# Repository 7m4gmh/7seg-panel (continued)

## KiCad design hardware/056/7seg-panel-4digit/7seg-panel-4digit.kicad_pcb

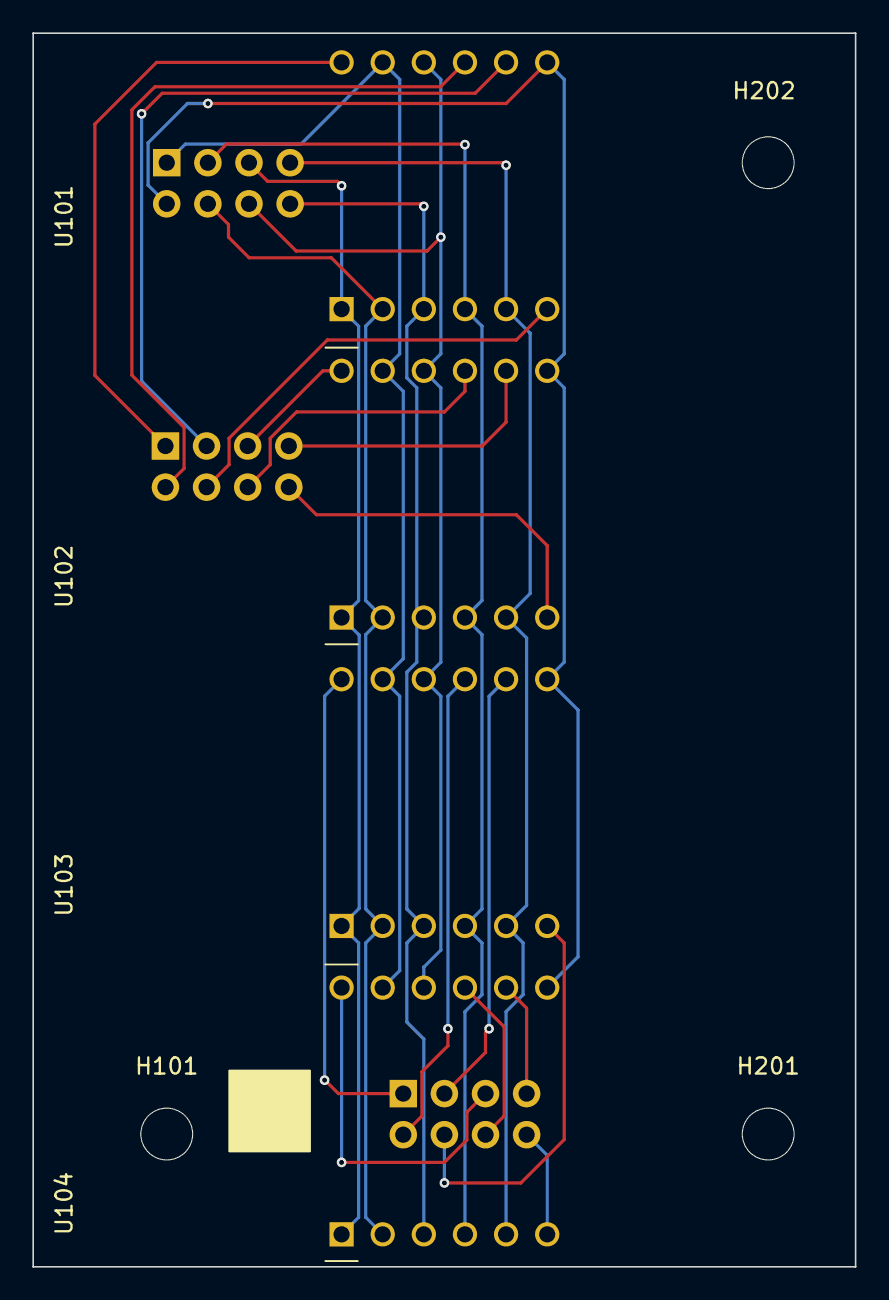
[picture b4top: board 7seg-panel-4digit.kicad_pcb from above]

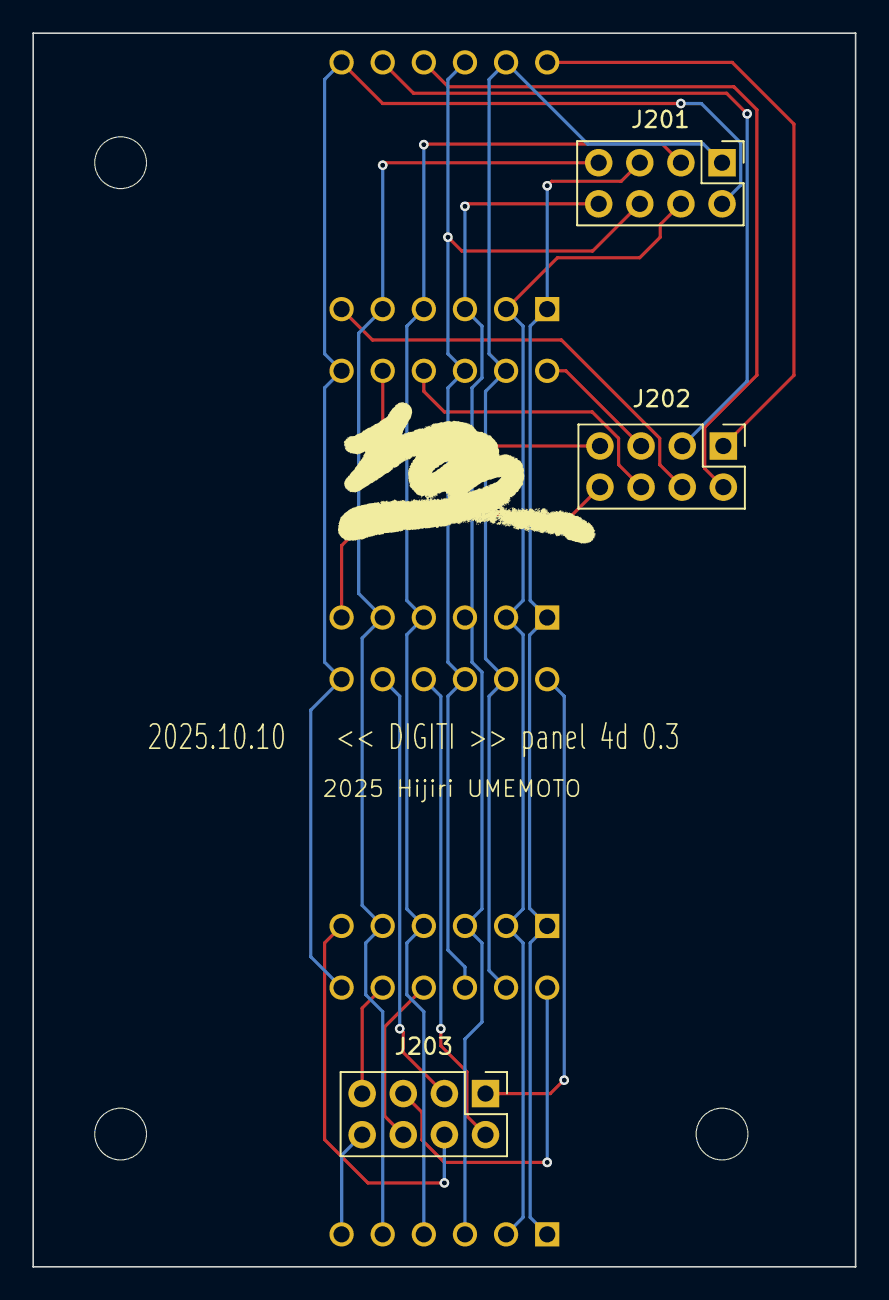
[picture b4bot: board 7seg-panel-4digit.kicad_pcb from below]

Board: 2 copper layers, 50.8 x 76.2 mm, 10 parts (3 on the bottom side), 24 nets.

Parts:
H101, H201, H202: MountingHole; MountingHole_3.2mm_M3
J201, J202, J203: Conn_02x04_Odd_Even; PinHeader_2x04_P2.54mm_Vertical
U101, U102, U103, U104: CA56-12EWA

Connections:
COM0: J201.1, U101.11 (a), U102.11 (a), U103.11 (a), U104.11 (a)
COM1: J201.2, U101.7 (b), U102.7 (b), U103.7 (b), U104.7 (b)
COM2: J201.3, U101.4 (c), U102.4 (c), U103.4 (c), U104.4 (c)
COM3: J201.4, U101.2 (d), U102.2 (d), U103.2 (d), U104.2 (d)
COM4: J201.5, U101.1 (e), U102.1 (e), U103.1 (e), U104.1 (e)
COM5: J201.6, U101.10 (f), U102.10 (f), U103.10 (f), U104.10 (f)
COM6: J201.7, U101.5 (g), U102.5 (g), U103.5 (g), U104.5 (g)
COM7: J201.8, U101.3 (DPX), U102.3 (DPX), U103.3 (DPX), U104.3 (DPX)
ROW0: J202.1, U101.12 (CA1)
ROW1: J202.2, U101.9 (CA2)
ROW2: J202.3, U101.8 (CA3)
ROW3: J202.4, U101.6 (CA4)
ROW4: J202.5, U102.12 (CA1)
ROW5: J202.6, U102.9 (CA2)
ROW6: J202.7, U102.8 (CA3)
ROW7: J202.8, U102.6 (CA4)
ROW8: J203.1, U103.12 (CA1)
ROW9: J203.2, U103.9 (CA2)
ROW10: J203.3, U103.8 (CA3)
ROW11: J203.4, U103.6 (CA4)
ROW12: J203.5, U104.12 (CA1)
ROW13: J203.6, U104.9 (CA2)
ROW14: J203.7, U104.8 (CA3)
ROW15: J203.8, U104.6 (CA4)

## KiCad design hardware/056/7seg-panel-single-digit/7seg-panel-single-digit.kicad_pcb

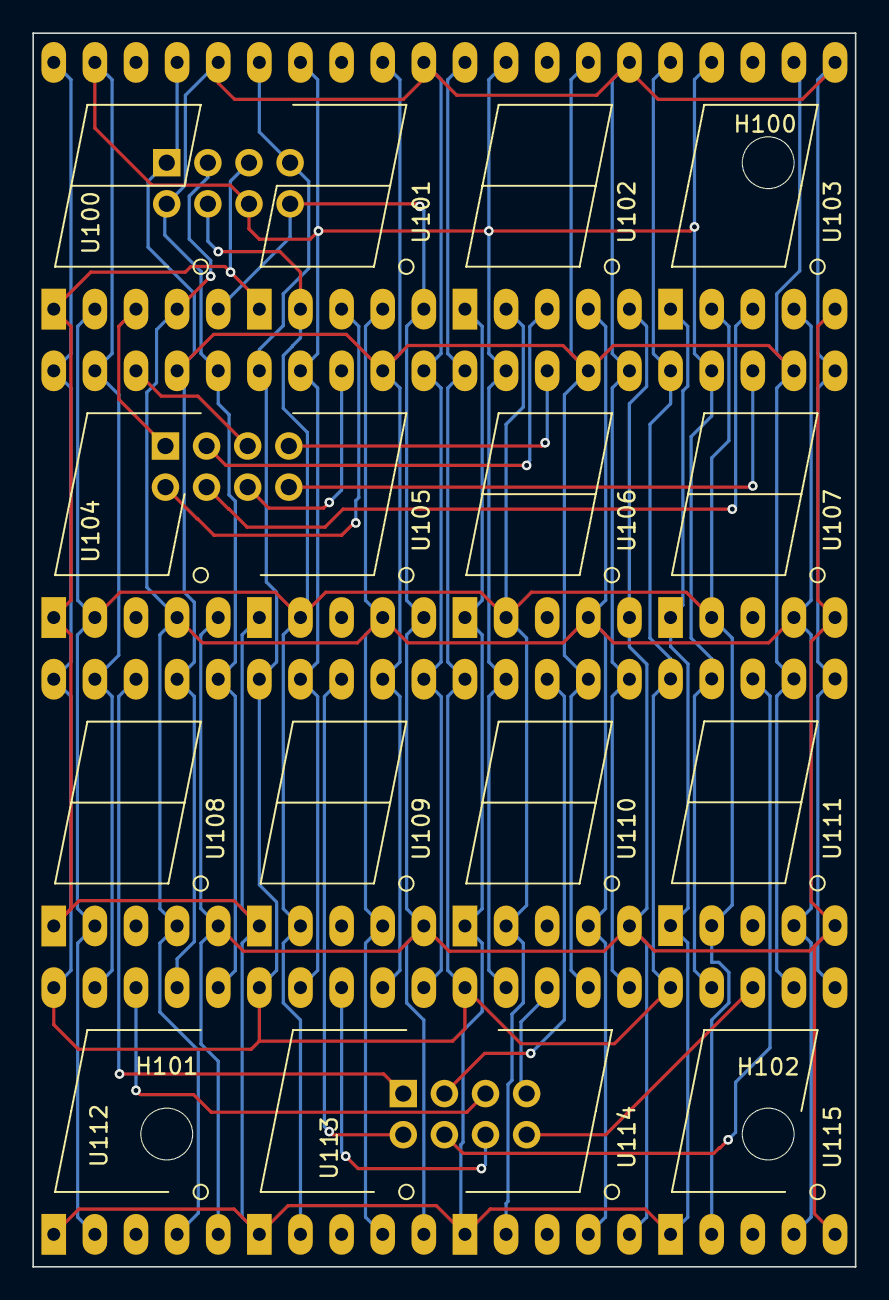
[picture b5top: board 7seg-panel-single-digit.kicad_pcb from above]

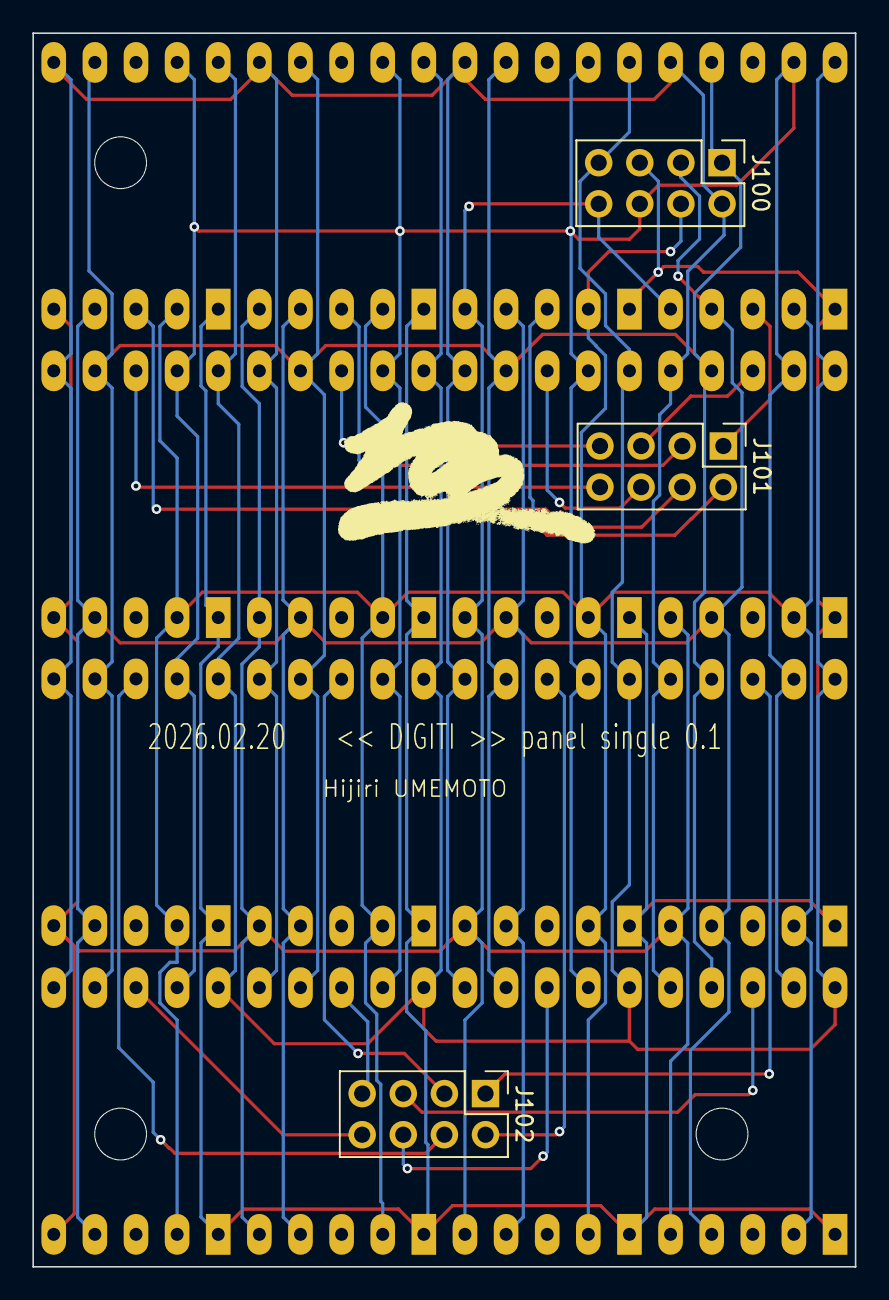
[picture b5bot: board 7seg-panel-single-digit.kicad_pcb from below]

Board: 2 copper layers, 50.8 x 76.2 mm, 22 parts (3 on the bottom side), 24 nets.

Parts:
H100, H101, H102: MountingHole; MountingHole_3.2mm_M3
J100, J101, J102: Conn_02x04_Odd_Even; PinHeader_2x04_P2.54mm_Vertical
U100, U101, U102, U103, U104, U105, U106, U107, U108, U109, U110, U111, U112, U113, U114, U115: OSL10564-IRA; 7SegmentLED_OSL10564

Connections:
COM0: J100.1, U100.7 (A), U101.7 (A), U102.7 (A), U103.7 (A), U104.7 (A), U105.7 (A), U106.7 (A), U107.7 (A), U108.7 (A), U109.7 (A), U110.7 (A), U111.7 (A), U112.7 (A), U113.7 (A), U114.7 (A), U115.7 (A)
COM1: J100.2, U100.6 (B), U101.6 (B), U102.6 (B), U103.6 (B), U104.6 (B), U105.6 (B), U106.6 (B), U107.6 (B), U108.6 (B), U109.6 (B), U110.6 (B), U111.6 (B), U112.6 (B), U113.6 (B), U114.6 (B), U115.6 (B)
COM2: J100.3, U100.4 (C), U101.4 (C), U102.4 (C), U103.4 (C), U104.4 (C), U105.4 (C), U106.4 (C), U107.4 (C), U108.4 (C), U109.4 (C), U110.4 (C), U111.4 (C), U112.4 (C), U113.4 (C), U114.4 (C), U115.4 (C)
COM3: J100.4, U100.2 (D), U101.2 (D), U102.2 (D), U103.2 (D), U104.2 (D), U105.2 (D), U106.2 (D), U107.2 (D), U108.2 (D), U109.2 (D), U110.2 (D), U111.2 (D), U112.2 (D), U113.2 (D), U114.2 (D), U115.2 (D)
COM4: J100.5, U100.1 (E), U101.1 (E), U102.1 (E), U103.1 (E), U104.1 (E), U105.1 (E), U106.1 (E), U107.1 (E), U108.1 (E), U109.1 (E), U110.1 (E), U111.1 (E), U112.1 (E), U113.1 (E), U114.1 (E), U115.1 (E)
COM5: J100.6, U100.9 (F), U101.9 (F), U102.9 (F), U103.9 (F), U104.9 (F), U105.9 (F), U106.9 (F), U107.9 (F), U108.9 (F), U109.9 (F), U110.9 (F), U111.9 (F), U112.9 (F), U113.9 (F), U114.9 (F), U115.9 (F)
COM6: J100.7, U100.10 (G), U101.10 (G), U102.10 (G), U103.10 (G), U104.10 (G), U105.10 (G), U106.10 (G), U107.10 (G), U108.10 (G), U109.10 (G), U110.10 (G), U111.10 (G), U112.10 (G), U113.10 (G), U114.10 (G), U115.10 (G)
COM7: J100.8, U100.5 (DP), U101.5 (DP), U102.5 (DP), U103.5 (DP), U104.5 (DP), U105.5 (DP), U106.5 (DP), U107.5 (DP), U108.5 (DP), U109.5 (DP), U110.5 (DP), U111.5 (DP), U112.5 (DP), U113.5 (DP), U114.5 (DP), U115.5 (DP)
ROW0: J101.1, U100.3 (CA)
ROW1: J101.2, U101.3 (CA)
ROW2: J101.3, U102.3 (CA)
ROW3: J101.4, U103.3 (CA)
ROW4: J101.5, U104.8 (CA)
ROW5: J101.6, U105.8 (CA)
ROW6: J101.7, U106.8 (CA)
ROW7: J101.8, U107.8 (CA)
ROW8: J102.1, U108.8 (CA)
ROW9: J102.2, U109.8 (CA)
ROW10: J102.3, U110.8 (CA)
ROW11: J102.4, U111.8 (CA)
ROW12: J102.5, U112.8 (CA)
ROW13: J102.6, U113.8 (CA)
ROW14: J102.7, U114.8 (CA)
ROW15: J102.8, U115.8 (CA)

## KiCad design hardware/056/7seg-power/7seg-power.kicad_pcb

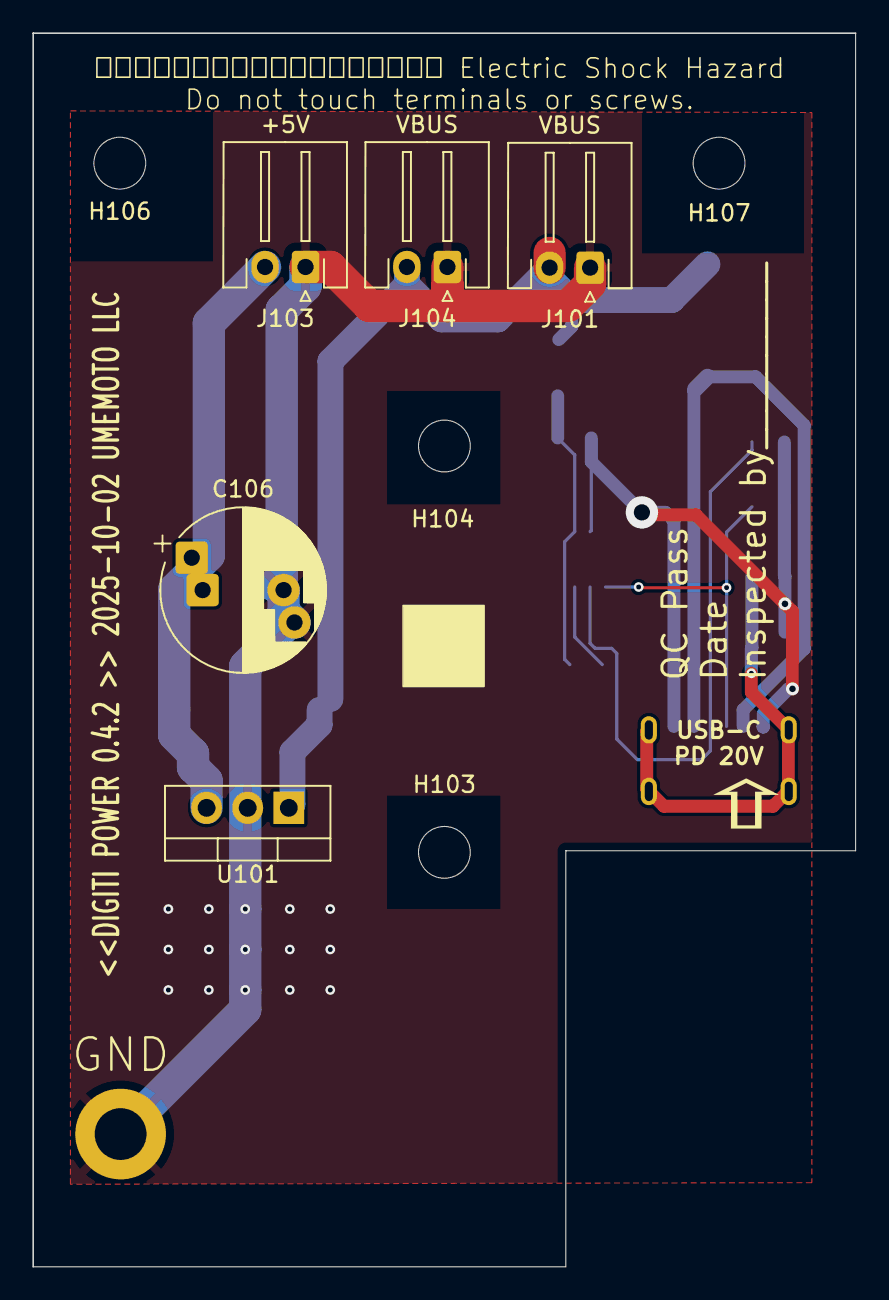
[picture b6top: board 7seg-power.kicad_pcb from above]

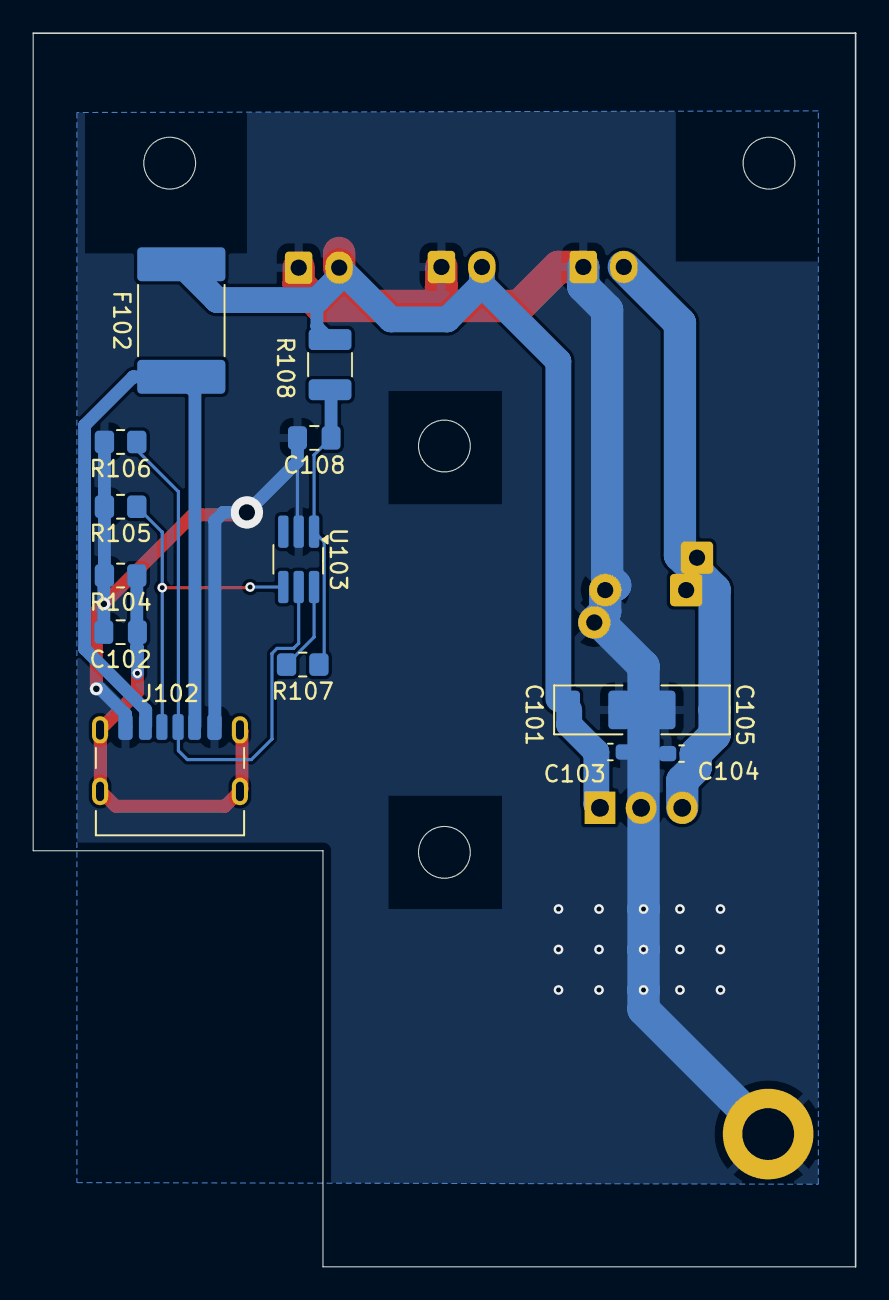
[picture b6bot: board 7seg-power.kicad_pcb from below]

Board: 2 copper layers, 50.8 x 76.2 mm, 24 parts (14 on the bottom side), 9 nets.

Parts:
C101, C105: 22uF; CP_EIA-3528-21_Kemet-B
C102: 4700pF (472); C_0805_2012Metric_Pad1.18x1.45mm_HandSolder
C103: 22uF 25V; C_0603_1608Metric_Pad1.08x0.95mm_HandSolder
C104: 22uF 6V; C_0603_1608Metric_Pad1.08x0.95mm_HandSolder
C106: 220uF; CP_Radial_D10.0mm_P5.00mm_P7.50mm
C108: 1uF; C_0805_2012Metric_Pad1.18x1.45mm_HandSolder
F102: Polyfuse 4A; Fuse_2920_7451Metric_Pad2.10x5.45mm_HandSolder
H102: GND; MountingHole_3.2mm_M3_DIN965_Pad
H103, H104, H106, H107: MountingHole; MountingHole_3.2mm_M3
J101, J104: VBUS; Generic_XH_S2B-XH-A-1_1x02_P2.50mm_Horizontal
J102: USB_C_Receptacle_PowerOnly_6P; USB_C_Receptacle_HRO_TYPE-C-31-M-17
J103: +5V; Generic_XH_S2B-XH-A-1_1x02_P2.50mm_Horizontal
R104: 1MR; R_0805_2012Metric_Pad1.20x1.40mm_HandSolder
R105, R106: 5k1R; R_0805_2012Metric_Pad1.20x1.40mm_HandSolder
R107: 200kR; R_0805_2012Metric_Pad1.20x1.40mm_HandSolder
R108: 1kR; R_1210_3225Metric_Pad1.30x2.65mm_HandSolder
U101: K7805M-2000; TO-220-3_Vertical
U103: CH221K; TSOT-23-6_HandSoldering

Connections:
+5V: C104.1, C105.1, C106.1, J103.2, U101.3 (VO)
GND: C101.2, C102.2, C103.2, C104.2, C105.2, C106.2, C108.2, H102.1 (MP), J101.1, J102.A12 (GND), J102.B12 (GND), J103.1, J104.1, R104.2, R105.2, R106.2, U101.2 (GND), U103.2 (GND)
unnamed: F102.1, J102.A9 (VBUS), J102.B9 (VBUS)
unnamed: J102.A5 (CC1), R105.1, U103.4 (CC1)
unnamed: J102.B5 (CC2), R106.1, U103.5 (CC2)
unnamed: C102.1, J102.S1 (SHIELD), R104.1
unnamed: R107.2, U103.6 (CFG)
unnamed: C108.1, R107.1, R108.1, U103.1 (VDD)
VBUS: C101.1, C103.1, F102.2, J101.2, J104.2, R108.2, U101.1 (VI)

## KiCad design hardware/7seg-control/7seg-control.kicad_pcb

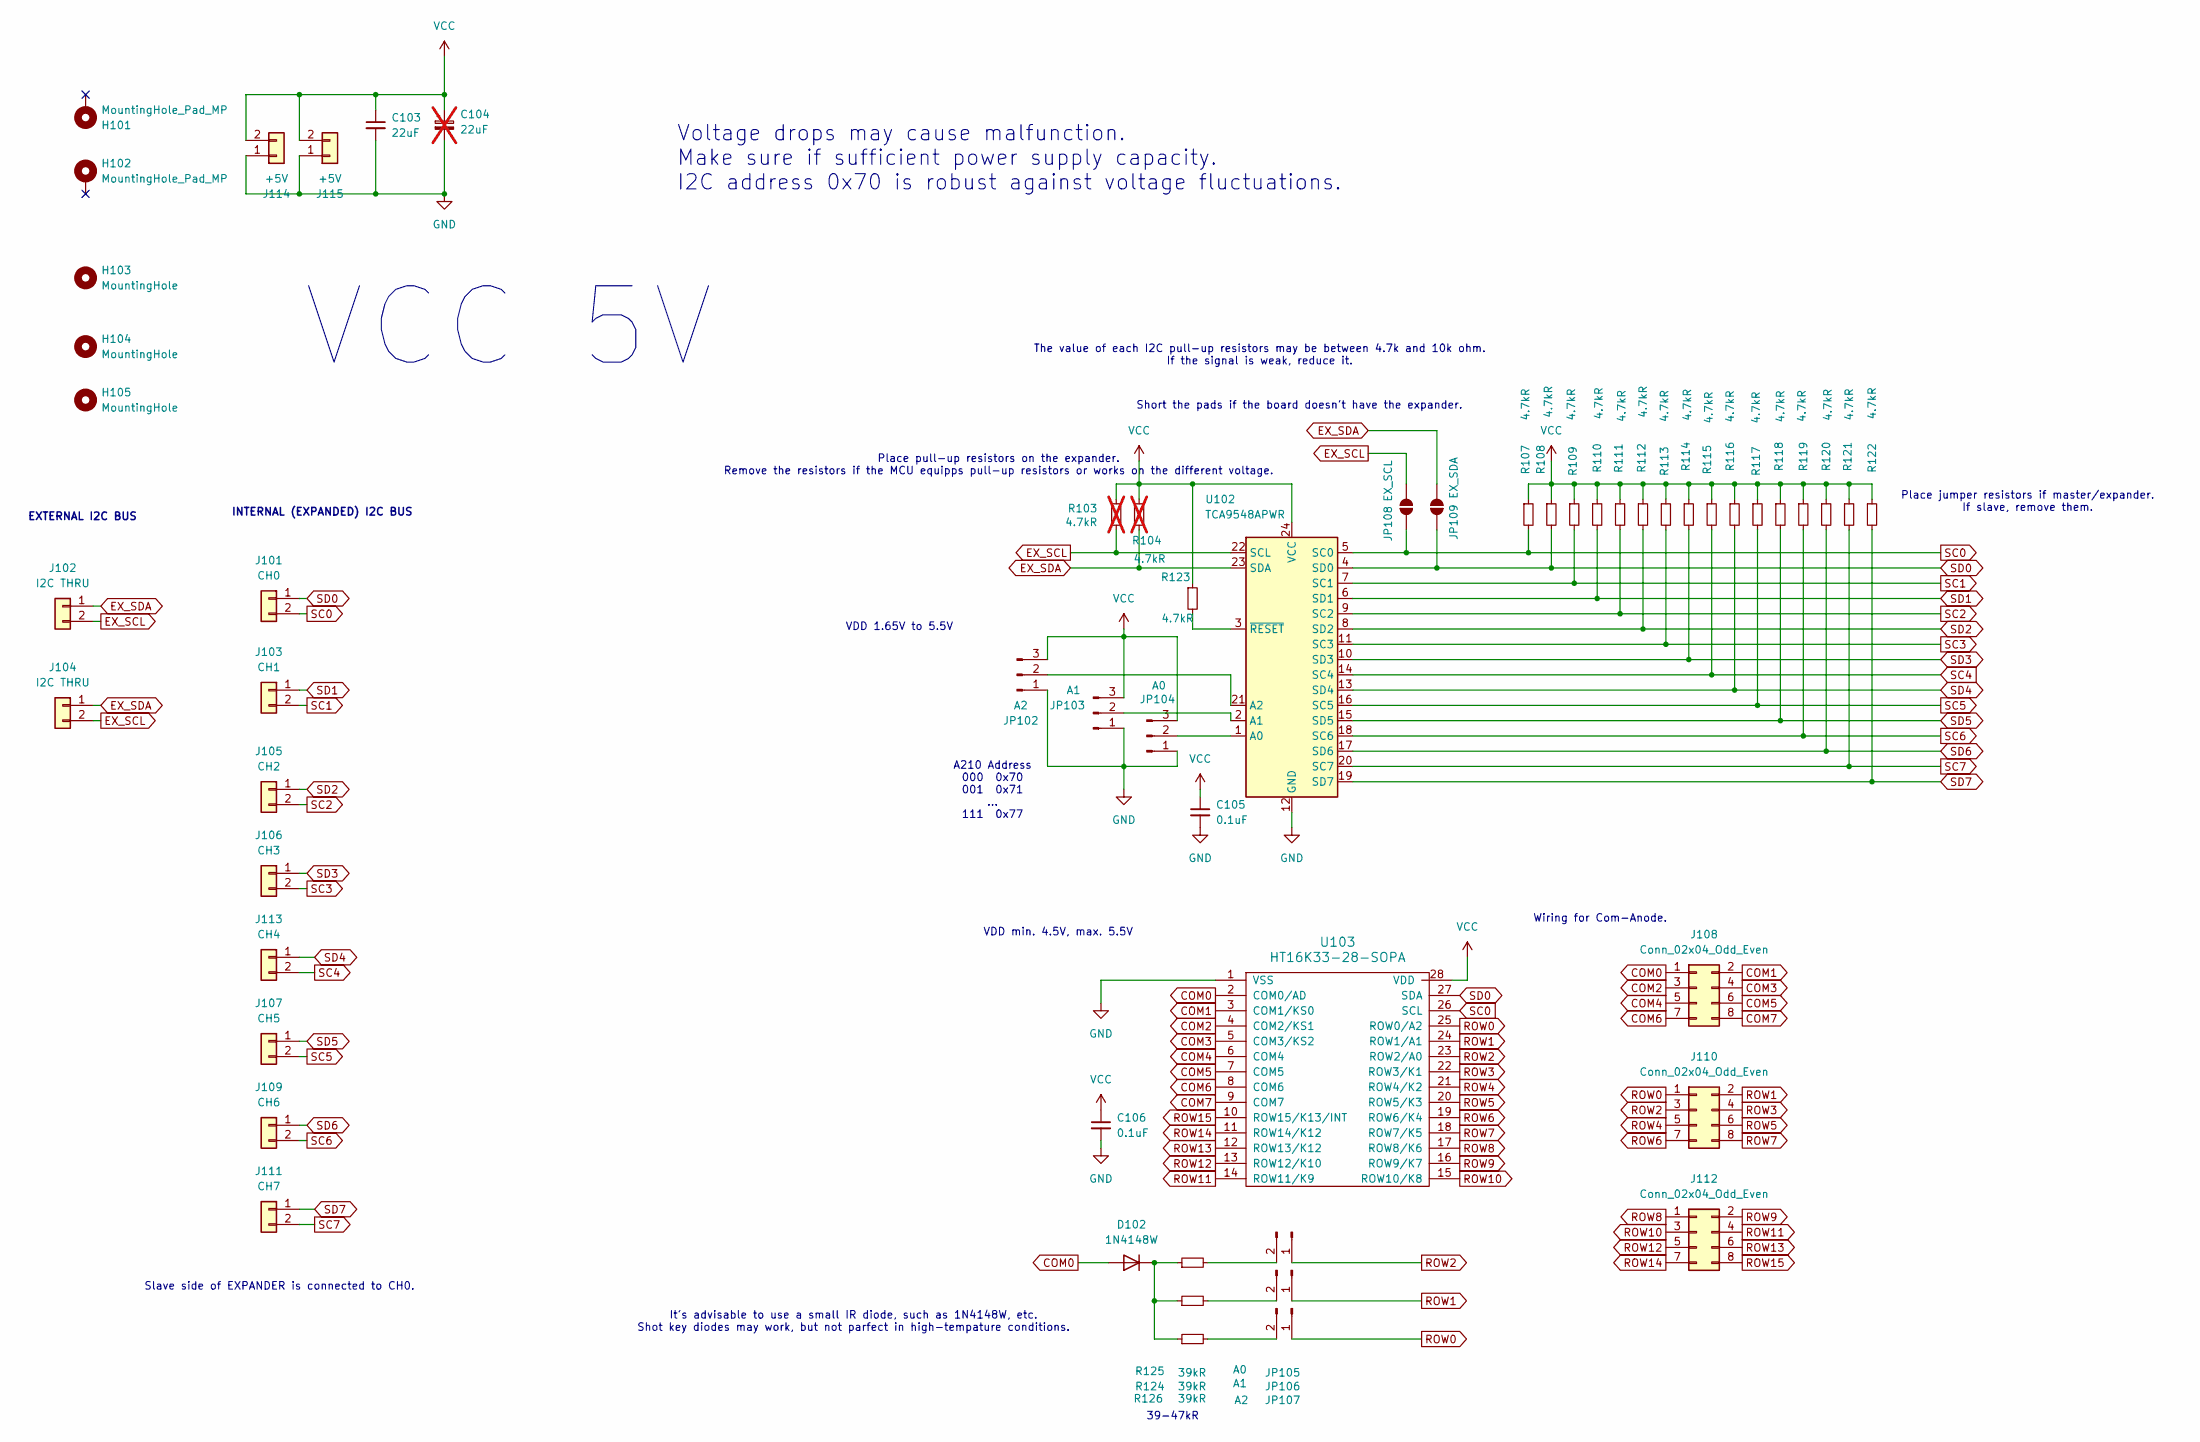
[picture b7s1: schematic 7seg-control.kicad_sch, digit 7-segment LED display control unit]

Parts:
C103: 22uF; C_0603_1608Metric
C104: 22uF; CP_EIA-3528-21_Kemet-B_HandSolder; not fitted
C105, C106: 0.1uF; C_0603_1608Metric_Pad1.08x0.95mm_HandSolder
D102: 1N4148W; D_SOD-123
H101, H102: MountingHole_Pad_MP; MountingHole_3.2mm_M3_DIN965_Pad
H103, H104, H105: MountingHole; MountingHole_3.2mm_M3
J101: CH0; Generic_XH_S2B-XH-A-1_1x02_P2.50mm_Horizontal
J102, J104: I2C THRU; JST_XH_B2B-XH-AM_1x02_P2.50mm_Vertical
J103: CH1; Generic_XH_S2B-XH-A-1_1x02_P2.50mm_Horizontal
J105: CH2; Generic_XH_S2B-XH-A-1_1x02_P2.50mm_Horizontal
J106: CH3; Generic_XH_S2B-XH-A-1_1x02_P2.50mm_Horizontal
J107: CH5; Generic_XH_S2B-XH-A-1_1x02_P2.50mm_Horizontal
J108, J110, J112: Conn_02x04_Odd_Even; PinSocket_2x04_P2.54mm_Vertical
J109: CH6; Generic_XH_S2B-XH-A-1_1x02_P2.50mm_Horizontal
J111: CH7; Generic_XH_S2B-XH-A-1_1x02_P2.50mm_Horizontal
J113: CH4; Generic_XH_S2B-XH-A-1_1x02_P2.50mm_Horizontal
J114, J115: +5V; JST_XH_B2B-XH-AM_1x02_P2.50mm_Vertical
JP102: A2; PinHeader_1x03_P2.54mm_Vertical
JP103: A1; PinHeader_1x03_P2.54mm_Vertical
JP104: A0; PinHeader_1x03_P2.54mm_Vertical
JP105: A0; PinHeader_1x02_P2.54mm_Vertical
JP106: A1; PinHeader_1x02_P2.54mm_Vertical
JP107: A2; PinHeader_1x02_P2.54mm_Vertical
JP108: EX_SCL; SolderJumper-2_P1.3mm_Open_TrianglePad1.0x1.5mm
JP109: EX_SDA; SolderJumper-2_P1.3mm_Open_TrianglePad1.0x1.5mm
R103, R104: 4.7kR; R_0603_1608Metric_Pad0.98x0.95mm_HandSolder; not fitted
R107, R108, R109, R110, R111, R112, R113, R114, R115, R116, R117, R118, R119, R120, R121, R122, R123: 4.7kR; R_0603_1608Metric_Pad0.98x0.95mm_HandSolder
R124, R125, R126: 39kR; R_0603_1608Metric_Pad0.98x0.95mm_HandSolder
U102: TCA9548APWR; TSSOP-24_4.4x7.8mm_P0.65mm
U103: HT16K33-28-SOPA; SOP-28_8.4x18.16mm_P1.27mm

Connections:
COM0: D102.2 (A), J108.1, U103.2 (COM0/AD)
COM1: J108.2, U103.3 (COM1/KS0)
COM2: J108.3, U103.4 (COM2/KS1)
COM3: J108.4, U103.5 (COM3/KS2)
COM4: J108.5, U103.6 (COM4)
COM5: J108.6, U103.7 (COM5)
COM6: J108.7, U103.8 (COM6)
COM7: J108.8, U103.9 (COM7)
EX_SCL: J102.2, J104.2, JP108.1 (A), R103.2, U102.22 (SCL)
EX_SDA: J102.1, J104.1, JP109.1 (A), R104.2, U102.23 (SDA)
GND: C103.2, C104.2, C105.2, C106.2, J114.1, J115.1, JP102.1, JP103.1, JP104.1, U102.12 (GND), U103.1 (VSS)
unnamed: D102.1 (K), R124.1, R125.1, R126.1
unnamed: JP102.2, U102.21 (A2)
unnamed: JP103.2, U102.2 (A1)
unnamed: JP104.2, U102.1 (A0)
unnamed: JP105.2, R124.2
unnamed: JP106.2, R125.2
unnamed: JP107.2, R126.2
unnamed: R123.2, U102.3 (~RESET)
ROW0: J110.1, JP107.1, U103.25 (ROW0/A2)
ROW1: J110.2, JP106.1, U103.24 (ROW1/A1)
ROW2: J110.3, JP105.1, U103.23 (ROW2/A0)
ROW3: J110.4, U103.22 (ROW3/K1)
ROW4: J110.5, U103.21 (ROW4/K2)
ROW5: J110.6, U103.20 (ROW5/K3)
ROW6: J110.7, U103.19 (ROW6/K4)
ROW7: J110.8, U103.18 (ROW7/K5)
ROW8: J112.1, U103.17 (ROW8/K6)
ROW9: J112.2, U103.16 (ROW9/K7)
ROW10: J112.3, U103.15 (ROW10/K8)
ROW11: J112.4, U103.14 (ROW11/K9)
ROW12: J112.5, U103.13 (ROW12/K10)
ROW13: J112.6, U103.12 (ROW13/K12)
ROW14: J112.7, U103.11 (ROW14/K12)
ROW15: J112.8, U103.10 (ROW15/K13/INT)
SC0: J101.2, JP108.2 (B), R107.2, U102.5 (SC0), U103.26 (SCL)
SC1: J103.2, R109.2, U102.7 (SC1)
SC2: J105.2, R111.2, U102.9 (SC2)
SC3: J106.2, R113.2, U102.11 (SC3)
SC4: J113.2, R115.2, U102.14 (SC4)
SC5: J107.2, R117.2, U102.16 (SC5)
SC6: J109.2, R119.2, U102.18 (SC6)
SC7: J111.2, R121.2, U102.20 (SC7)
SD0: J101.1, JP109.2 (B), R108.2, U102.4 (SD0), U103.27 (SDA)
SD1: J103.1, R110.2, U102.6 (SD1)
SD2: J105.1, R112.2, U102.8 (SD2)
SD3: J106.1, R114.2, U102.10 (SD3)
SD4: J113.1, R116.2, U102.13 (SD4)
SD5: J107.1, R118.2, U102.15 (SD5)
SD6: J109.1, R120.2, U102.17 (SD6)
SD7: J111.1, R122.2, U102.19 (SD7)
VCC: C103.1, C104.1, C105.1, C106.1, J114.2, J115.2, JP102.3, JP103.3, JP104.3, R103.1, R104.1, R107.1, R108.1, R109.1, R110.1, R111.1, R112.1, R113.1, R114.1, R115.1, R116.1, R117.1, R118.1, R119.1, R120.1, R121.1, R122.1, R123.1, U102.24 (VCC), U103.28 (VDD)

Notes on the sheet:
A210 Address 000 0x70 001 0x71 ... 111 0x77
Place jumper resistors if master/expander. If slave, remove them.
Voltage drops may cause malfunction. Make sure if sufficient power supply capacity. I2C address 0x70 is robust against voltage fluctuations.
39-47kR
It's advisable to use a small IR diode, such as 1N4148W, etc. Shot key diodes may work, but not parfect in high-tempature conditions.
Wiring for Com-Anode.
VCC 5V
Slave side of EXPANDER is connected to CH0.
Place pull-up resistors on the expander. Remove the resistors if the MCU equipps pull-up resistors or works on the different voltage.
Short the pads if the board doesn't have the expander.
EXTERNAL I2C BUS
The value of each I2C pull-up resistors may be between 4.7k and 10k ohm. If the signal is weak, reduce it.
VDD 1.65V to 5.5V
INTERNAL (EXPANDED) I2C BUS
VDD min. 4.5V, max. 5.5V

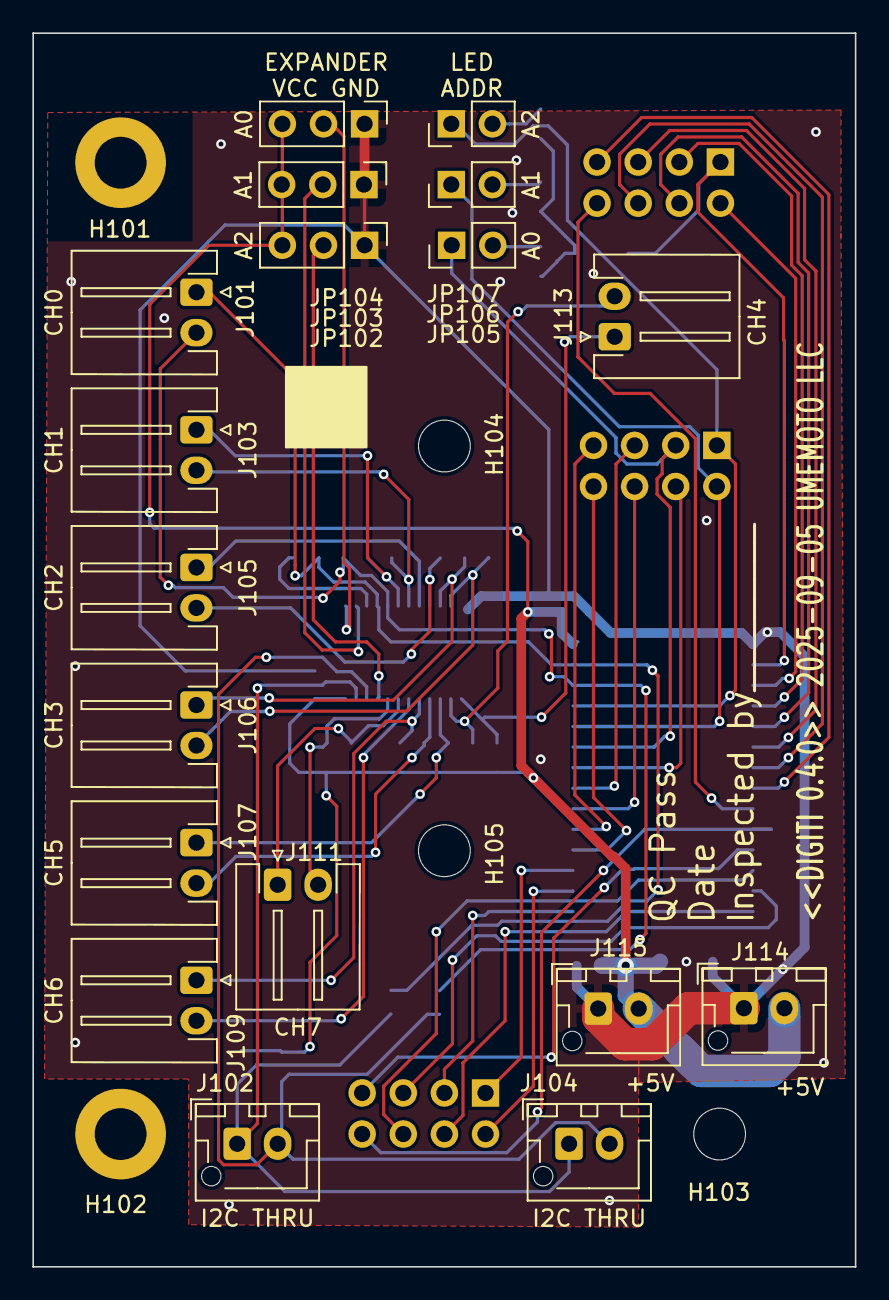
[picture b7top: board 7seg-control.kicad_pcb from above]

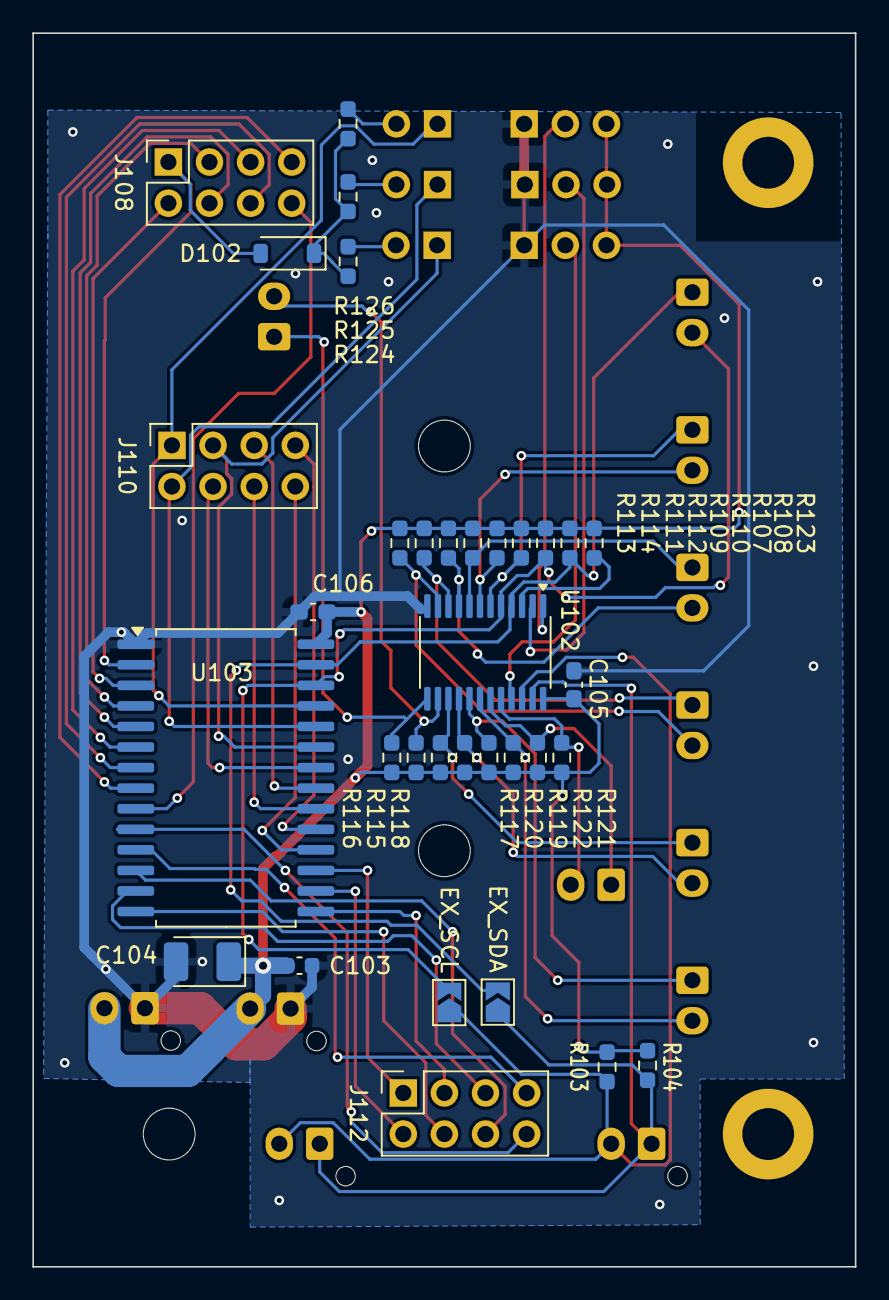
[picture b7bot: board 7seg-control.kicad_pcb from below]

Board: 2 copper layers, 50.8 x 76.2 mm, 57 parts (34 on the bottom side), 52 nets.

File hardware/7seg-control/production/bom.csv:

Designator,Footprint,Quantity,Value,LCSC Part #
C103,0603,1,22uF,
"C105, C106",0603,2,0.1uF,
D102,D_SOD-123,1,1N4148W,
J101,Generic_XH_S2B-XH-A-1_1x02_P2.50mm_Horizontal,1,CH0,
"J102, J104",JST_XH_B2B-XH-AM_1x02_P2.50mm_Vertical,2,I2C THRU,
J103,Generic_XH_S2B-XH-A-1_1x02_P2.50mm_Horizontal,1,CH1,
J105,Generic_XH_S2B-XH-A-1_1x02_P2.50mm_Horizontal,1,CH2,
J106,Generic_XH_S2B-XH-A-1_1x02_P2.50mm_Horizontal,1,CH3,
J107,Generic_XH_S2B-XH-A-1_1x02_P2.50mm_Horizontal,1,CH5,
"J108, J110, J112",PinSocket_2x04_P2.54mm_Vertical,3,Conn_02x04_Odd_Even,
J109,Generic_XH_S2B-XH-A-1_1x02_P2.50mm_Horizontal,1,CH6,
J111,Generic_XH_S2B-XH-A-1_1x02_P2.50mm_Horizontal,1,CH7,
J113,Generic_XH_S2B-XH-A-1_1x02_P2.50mm_Horizontal,1,CH4,
"J114, J115",JST_XH_B2B-XH-AM_1x02_P2.50mm_Vertical,2,+5V,
JP102,PinHeader_1x03_P2.54mm_Vertical,1,A2,
JP103,PinHeader_1x03_P2.54mm_Vertical,1,A1,
JP104,PinHeader_1x03_P2.54mm_Vertical,1,A0,
JP105,PinHeader_1x02_P2.54mm_Vertical,1,A0,
JP106,PinHeader_1x02_P2.54mm_Vertical,1,A1,
JP107,PinHeader_1x02_P2.54mm_Vertical,1,A2,
"R107, R108, R109, R110, R111, R112, R113, R114, R115, R116, R117, R118, R119, R120, R121, R122, R123",0603,17,4.7kR,
"R124, R125, R126",0603,3,39kR,
U102,TSSOP-24_4.4x7.8mm_P0.65mm,1,TCA9548APWR,
U103,SOP-28_8.4x18.16mm_P1.27mm,1,HT16K33-28-SOPA,

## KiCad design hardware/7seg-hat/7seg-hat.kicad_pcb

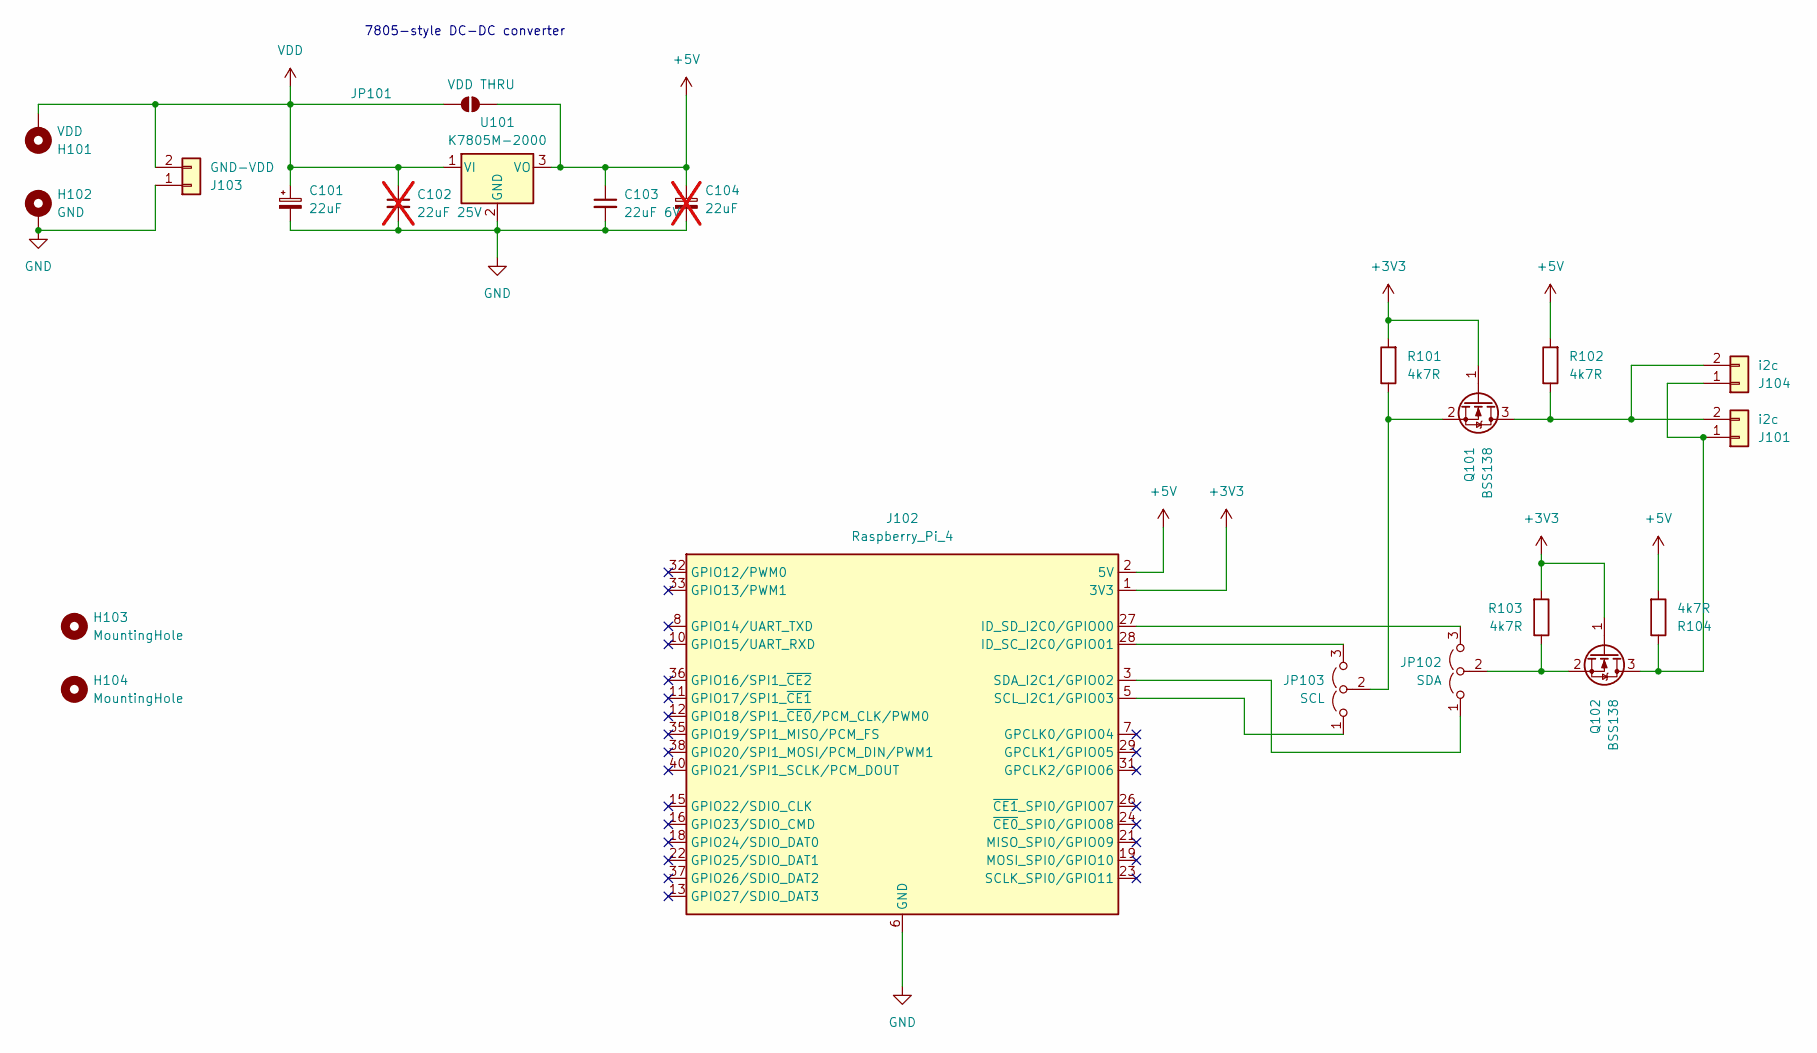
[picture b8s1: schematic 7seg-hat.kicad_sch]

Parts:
C101: 22uF; CP_EIA-3528-21_Kemet-B
C102: 22uF 25V; C_0603_1608Metric_Pad1.08x0.95mm_HandSolder; not fitted
C103: 22uF 6V; C_0603_1608Metric_Pad1.08x0.95mm_HandSolder
C104: 22uF; CP_EIA-3528-21_Kemet-B; not fitted
H101: VDD; MountingHole_3.2mm_M3_DIN965_Pad
H102: GND; MountingHole_3.2mm_M3_DIN965_Pad
H103, H104: MountingHole; MountingHole_3.2mm_M3
J101, J104: i2c; JST_XH_S2B-XH-A-1_1x02_P2.50mm_Horizontal
J102: Raspberry_Pi_4; RPI_Hat_B+
J103: GND-VDD; JST_XH_S2B-XH-A-1_1x02_P2.50mm_Horizontal
JP101: VDD THRU; SolderJumper-2_P1.3mm_Open_TrianglePad1.0x1.5mm
JP102: SDA; PinHeader_1x03_P2.54mm_Vertical
JP103: SCL; PinHeader_1x03_P2.54mm_Vertical
Q101, Q102: BSS138; SOT-23_Handsoldering
R101, R102, R103, R104: 4k7R; R_0603_1608Metric_Pad0.98x0.95mm_HandSolder
U101: K7805M-2000; TO-220-3_Vertical

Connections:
+3V3: J102.1 (3V3), J102.17 (3V3), Q101.1 (G), Q102.1 (G), R101.2, R103.2
+5V: C103.1, C104.1, J102.2 (5V), J102.4 (5V), JP101.2 (B), R102.2, R104.2, U101.3 (VO)
GND: C101.2, C102.2, C103.2, C104.2, H102.1 (MP), J102.6 (GND), J102.9 (GND), J102.14 (GND), J102.20 (GND), J102.25 (GND), J102.30 (GND), J102.34 (GND), J102.39 (GND), J103.1, U101.2 (GND)
unnamed: J101.1, J104.1, Q102.3 (D), R104.1
unnamed: J101.2, J104.2, Q101.3 (D), R102.1
unnamed: J102.28 (ID_SC_I2C0/GPIO01), JP103.3 (B)
unnamed: J102.27 (ID_SD_I2C0/GPIO00), JP102.3 (B)
unnamed: J102.5 (SCL_I2C1/GPIO03), JP103.1 (A)
unnamed: J102.3 (SDA_I2C1/GPIO02), JP102.1 (A)
unnamed: JP102.2 (C), Q102.2 (S), R103.1
unnamed: JP103.2 (C), Q101.2 (S), R101.1
VDD: C101.1, C102.1, H101.1 (MP), J103.2, JP101.1 (A), U101.1 (VI)

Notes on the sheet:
7805-style DC-DC converter
